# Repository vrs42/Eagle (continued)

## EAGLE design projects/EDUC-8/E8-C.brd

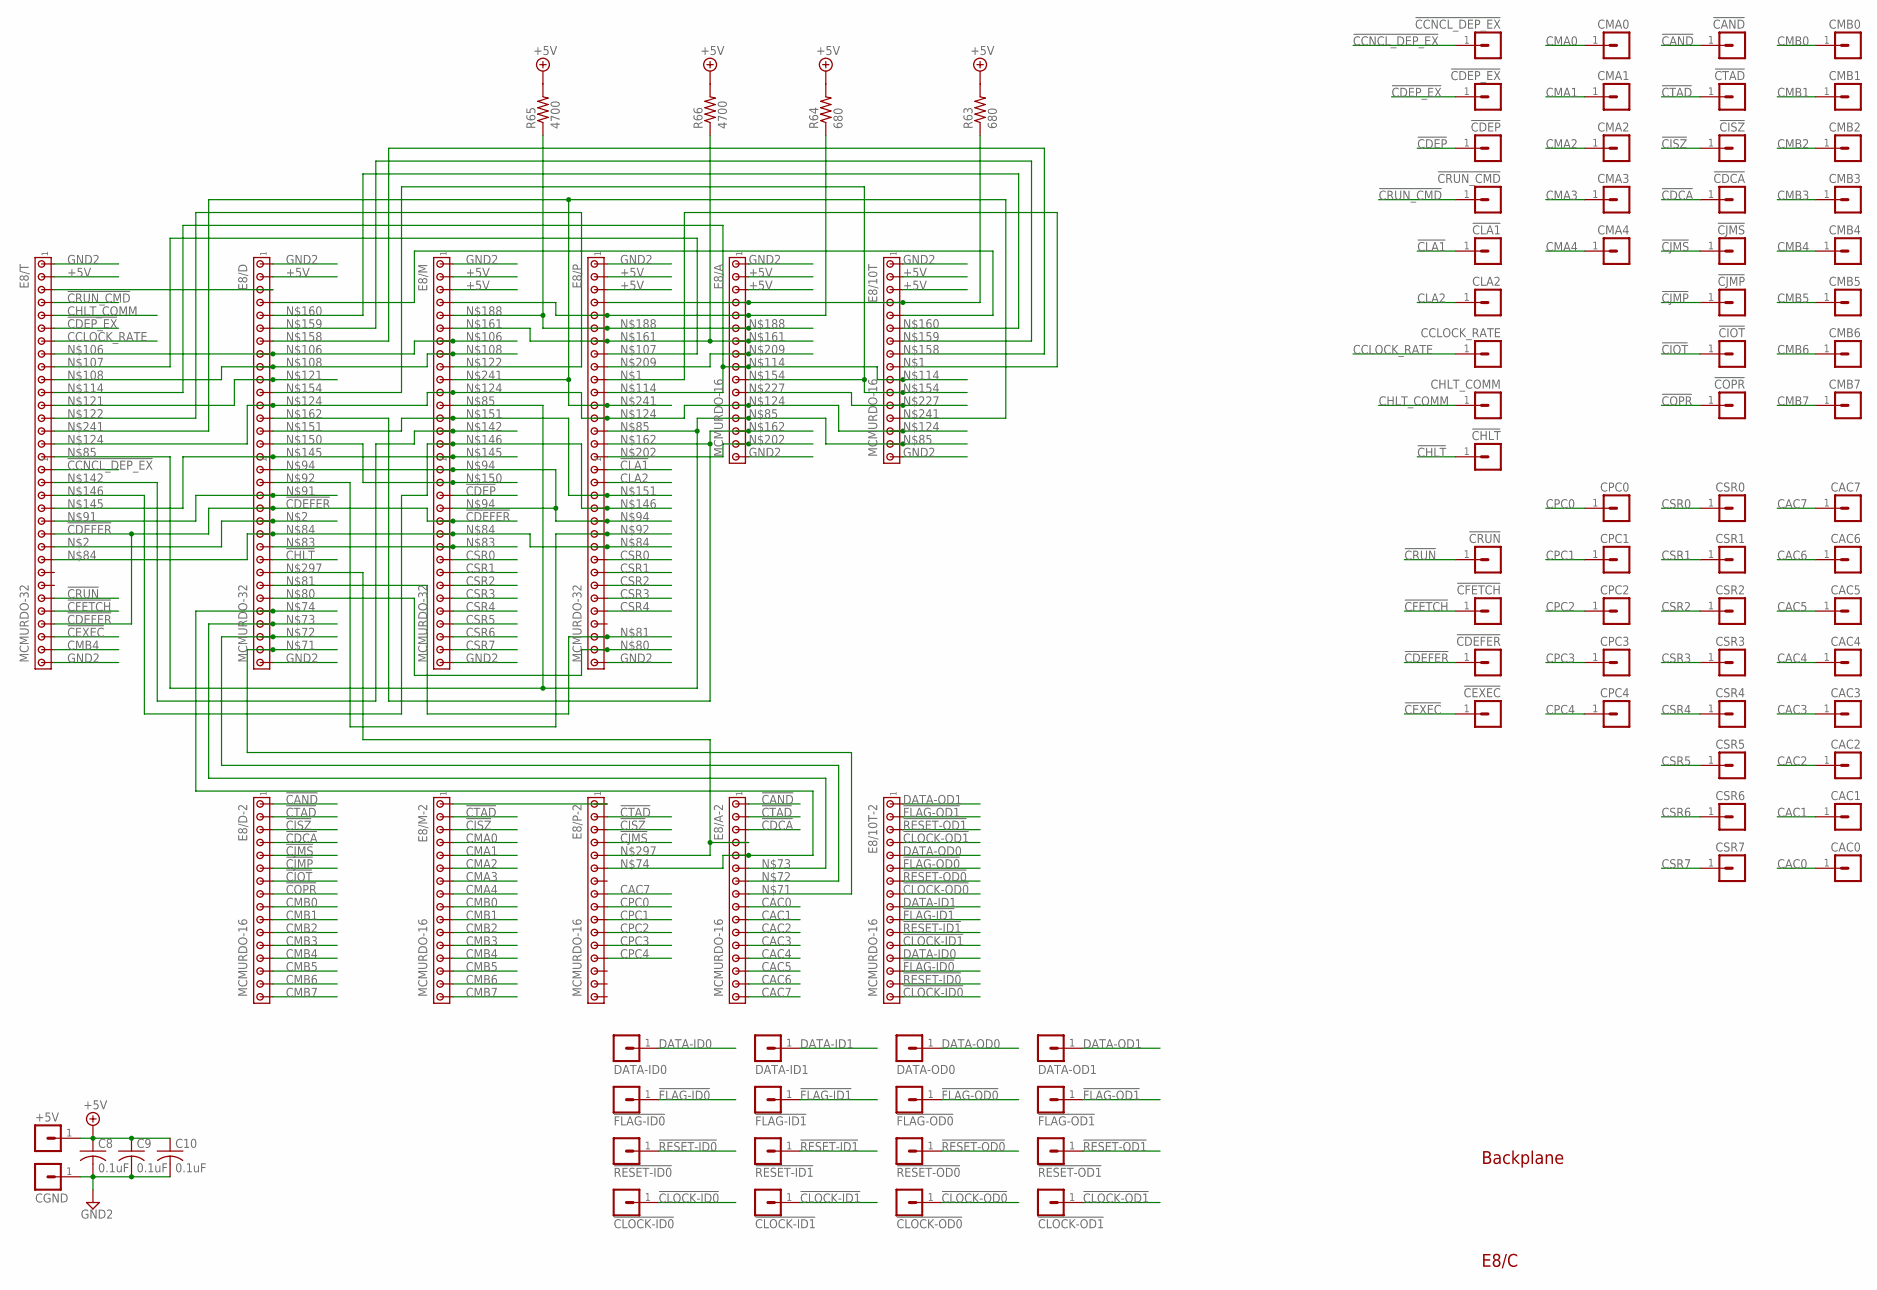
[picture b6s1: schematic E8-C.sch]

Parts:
!CAND: MA01-1
!CCNCL_DEP_EX: MA01-1
!CDCA: MA01-1
!CDEFER: MA01-1
!CDEP: MA01-1
!CDEP_EX: MA01-1
!CEXEC: MA01-1
!CFETCH: MA01-1
!CHLT: MA01-1
!CIOT: MA01-1
!CISZ: MA01-1
!CJMP: MA01-1
!CJMS: MA01-1
!CLA1: MA01-1
!CLOCK-ID0, !CLOCK-ID1: MA01-1
!CLOCK-OD0, !CLOCK-OD1: MA01-1
!COPR: MA01-1
!CRUN: MA01-1
!CRUN_CMD: MA01-1
!CTAD: MA01-1
!FLAG-ID0, !FLAG-ID1: MA01-1
!FLAG-OD0, !FLAG-OD1: MA01-1
!RESET-ID0, !RESET-ID1: MA01-1
!RESET-OD0, !RESET-OD1: MA01-1
+5V: MA01-1
C8, C9, C10: 0.1uF; C075-032X103
CAC0, CAC1, CAC2, CAC3, CAC4, CAC5, CAC6, CAC7: MA01-1
CCLOCK_RATE: MA01-1
CGND: MA01-1
CHLT_COMM: MA01-1
CLA2: MA01-1
CMA0, CMA1, CMA2, CMA3, CMA4: MA01-1
CMB0, CMB1, CMB2, CMB3, CMB4, CMB5, CMB6, CMB7: MA01-1
CPC0, CPC1, CPC2, CPC3, CPC4: MA01-1
CSR0, CSR1, CSR2, CSR3, CSR4, CSR5, CSR6, CSR7: MA01-1
DATA-ID0, DATA-ID1: MA01-1
DATA-OD0, DATA-OD1: MA01-1
E8/10T, E8/10T-2, E8/A, E8/A-2, E8/D-2, E8/M-2, E8/P-2: MCMURDO-16; 133-12-17
E8/D, E8/M, E8/P, E8/T: MCMURDO-32; 133-14-17
R63, R64: 680; 0207/15
R65, R66: 4700; 0207/15

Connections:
!CAND: !CAND.1, E8/A-2.1, E8/D-2.1
!CCNCL_DEP_EX: !CCNCL_DEP_EX.1, E8/T.17
!CDCA: !CDCA.1, E8/A-2.3, E8/D-2.4
!CDEFER: !CDEFER.1, E8/D.20, E8/M.21, E8/T.22, E8/T.29
!CDEP: !CDEP.1, E8/M.19
!CDEP_EX: !CDEP_EX.1, E8/T.6
!CEXEC: !CEXEC.1, E8/T.30
!CFETCH: !CFETCH.1, E8/T.28
!CHLT: !CHLT.1, E8/D.24
!CIOT: !CIOT.1, E8/D-2.7
!CISZ: !CISZ.1, E8/D-2.3, E8/M-2.3, E8/P-2.3
!CJMP: !CJMP.1, E8/D-2.6
!CJMS: !CJMS.1, E8/D-2.5, E8/P-2.4
!CLA1: !CLA1.1, E8/P.17
!CLOCK-ID0: !CLOCK-ID0.1, E8/10T-2.16
!CLOCK-ID1: !CLOCK-ID1.1, E8/10T-2.12
!CLOCK-OD0: !CLOCK-OD0.1, E8/10T-2.8
!CLOCK-OD1: !CLOCK-OD1.1, E8/10T-2.4
!COPR: !COPR.1, E8/D-2.8
!CRUN: !CRUN.1, E8/T.27
!CRUN_CMD: !CRUN_CMD.1, E8/T.4
!CTAD: !CTAD.1, E8/A-2.2, E8/D-2.2, E8/M-2.2, E8/P-2.2
!FLAG-ID0: !FLAG-ID0.1, E8/10T-2.14
!FLAG-ID1: !FLAG-ID1.1, E8/10T-2.10
!FLAG-OD0: !FLAG-OD0.1, E8/10T-2.6
!FLAG-OD1: !FLAG-OD1.1, E8/10T-2.2
!RESET-ID0: !RESET-ID0.1, E8/10T-2.15
!RESET-ID1: !RESET-ID1.1, E8/10T-2.11
!RESET-OD0: !RESET-OD0.1, E8/10T-2.7
!RESET-OD1: !RESET-OD1.1, E8/10T-2.3
+5V: +5V.1, C8.1, C9.1, C10.1, E8/10T.2, E8/10T.3, E8/A.2, E8/A.3, E8/D.2, E8/M.2, E8/M.3, E8/P.2, E8/P.3, E8/T.2, R63.2, R64.2, R65.2, R66.2
CAC0: CAC0.1, E8/A-2.9
CAC1: CAC1.1, E8/A-2.10
CAC2: CAC2.1, E8/A-2.11
CAC3: CAC3.1, E8/A-2.12
CAC4: CAC4.1, E8/A-2.13
CAC5: CAC5.1, E8/A-2.14
CAC6: CAC6.1, E8/A-2.15
CAC7: CAC7.1, E8/A-2.16, E8/P-2.8
CCLOCK_RATE: CCLOCK_RATE.1, E8/T.7
CHLT_COMM: CHLT_COMM.1, E8/T.5
CLA2: CLA2.1, E8/P.18
CMA0: CMA0.1, E8/M-2.4
CMA1: CMA1.1, E8/M-2.5
CMA2: CMA2.1, E8/M-2.6
CMA3: CMA3.1, E8/M-2.7
CMA4: CMA4.1, E8/M-2.8
CMB0: CMB0.1, E8/D-2.9, E8/M-2.9
CMB1: CMB1.1, E8/D-2.10, E8/M-2.10
CMB2: CMB2.1, E8/D-2.11, E8/M-2.11
CMB3: CMB3.1, E8/D-2.12, E8/M-2.12
CMB4: CMB4.1, E8/D-2.13, E8/M-2.13, E8/T.31
CMB5: CMB5.1, E8/D-2.14, E8/M-2.14
CMB6: CMB6.1, E8/D-2.15, E8/M-2.15
CMB7: CMB7.1, E8/D-2.16, E8/M-2.16
CPC0: CPC0.1, E8/P-2.9
CPC1: CPC1.1, E8/P-2.10
CPC2: CPC2.1, E8/P-2.11
CPC3: CPC3.1, E8/P-2.12
CPC4: CPC4.1, E8/P-2.13
CSR0: CSR0.1, E8/M.24, E8/P.24
CSR1: CSR1.1, E8/M.25, E8/P.25
CSR2: CSR2.1, E8/M.26, E8/P.26
CSR3: CSR3.1, E8/M.27, E8/P.27
CSR4: CSR4.1, E8/M.28, E8/P.28
CSR5: CSR5.1, E8/M.29
CSR6: CSR6.1, E8/M.30
CSR7: CSR7.1, E8/M.31
DATA-ID0: DATA-ID0.1, E8/10T-2.13
DATA-ID1: DATA-ID1.1, E8/10T-2.9
DATA-OD0: DATA-OD0.1, E8/10T-2.5
DATA-OD1: DATA-OD1.1, E8/10T-2.1
GND2: C8.2, C9.2, C10.2, CGND.1, E8/10T.1, E8/10T.16, E8/A.1, E8/A.16, E8/D.1, E8/D.32, E8/M.1, E8/M.32, E8/P.1, E8/P.32, E8/T.1, E8/T.32
unnamed: E8/10T.9, E8/P.10
unnamed: E8/D.21, E8/T.23
unnamed: E8/10T.5, E8/D.4
unnamed: E8/A-2.8, E8/D.31
unnamed: E8/A-2.7, E8/D.30
unnamed: E8/A-2.6, E8/D.29
unnamed: E8/A-2.5, E8/D.28, E8/P-2.6
unnamed: E8/D.27, E8/P.31
unnamed: E8/D.26, E8/P.30
unnamed: E8/D.23, E8/M.23
unnamed: E8/D.22, E8/M.22, E8/P.23, E8/T.24
unnamed: E8/10T.15, E8/A.13, E8/M.12, E8/P.14, E8/T.16
unnamed: E8/D.3, E8/T.3
unnamed: E8/D.19, E8/T.21
unnamed: E8/D.18, E8/P.22
unnamed: E8/D.17, E8/M.17, E8/M.20, E8/P.21
unnamed: E8/D.8, E8/M.7, E8/T.8
unnamed: E8/P.8, E8/T.9
unnamed: E8/D.9, E8/M.8, E8/T.10
unnamed: E8/10T.10, E8/A.9, E8/P.11, E8/T.11
unnamed: E8/D.10, E8/T.12
unnamed: E8/M.9, E8/T.13
unnamed: E8/10T.14, E8/A.12, E8/D.12, E8/M.11, E8/P.13, E8/T.15
unnamed: E8/M.14, E8/T.18
unnamed: E8/D.16, E8/M.16, E8/T.20
unnamed: E8/M.15, E8/P.20, E8/T.19
unnamed: E8/D.15, E8/M.18
unnamed: E8/D.14, E8/M.13, E8/P.19
unnamed: E8/10T.11, E8/A.10, E8/D.11
unnamed: E8/10T.8, E8/D.7
unnamed: E8/10T.7, E8/D.6
unnamed: E8/10T.6, E8/D.5
unnamed: E8/A.7, E8/M.6, E8/P.7, R66.1
unnamed: E8/A.14, E8/D.13, E8/P.15
unnamed: E8/A.5, E8/M.4, E8/P.5, R64.1
unnamed: E8/A.6, E8/M.5, E8/P.6, R65.1
unnamed: E8/A.15, E8/P.16
unnamed: E8/A.8, E8/P.9
unnamed: E8/10T.4, E8/A.4, E8/P.4, R63.1
unnamed: E8/10T.12, E8/A.11
unnamed: E8/10T.13, E8/M.10, E8/P.12, E8/T.14
unnamed: E8/M-2.1, E8/P-2.1
unnamed: E8/A-2.4, E8/D.25, E8/P-2.5

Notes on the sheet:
Backplane
E8/C

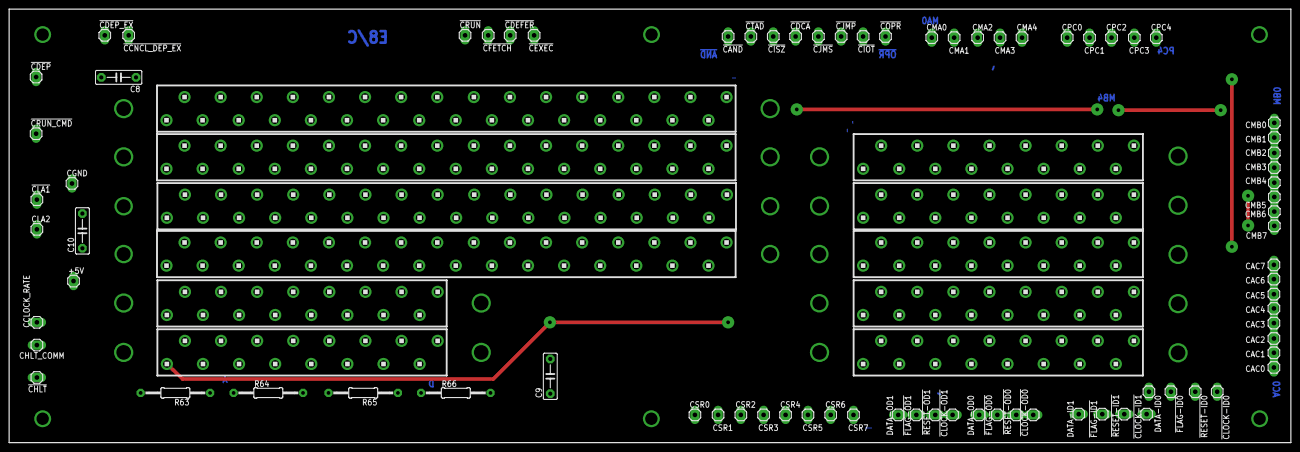
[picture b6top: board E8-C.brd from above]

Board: 2 copper layers, 281.3 x 95.2 mm, 91 parts (0 on the bottom side), 116 nets.
